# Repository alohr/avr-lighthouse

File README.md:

avr-lighthouse
==============

A photoresistor controlled LED blinker

http://ubiyubix.wordpress.com/2014/01/04/an-avr-and-photoresistor-controlled-lego-lighthouse/

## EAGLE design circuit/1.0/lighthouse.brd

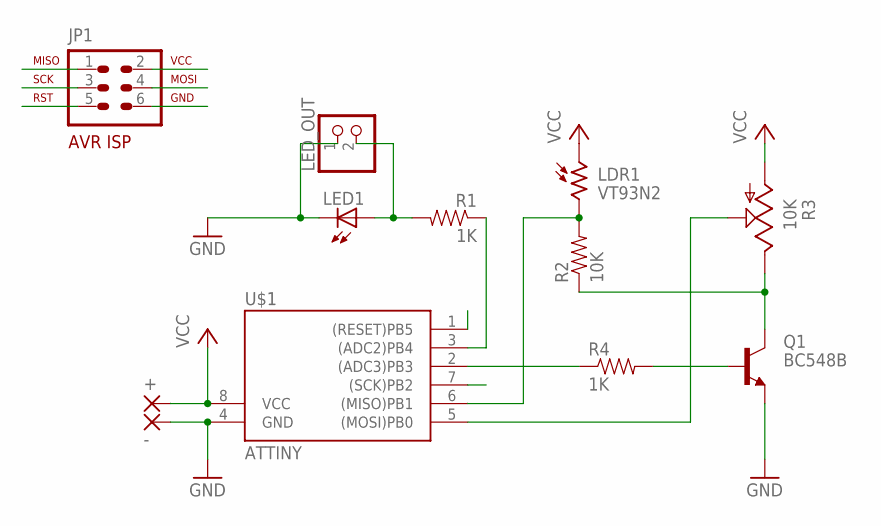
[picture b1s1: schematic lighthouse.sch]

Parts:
+: PAD-TERMINAL; 2,54/1,1
-: PAD-TERMINAL; 2,54/1,1
JP1: AVR-ISP-6VERT; AVR-ISP-6
LDR1: VT93N2; VT900
LED1: LED-3MM-NO_SILK; LED3MM-NS
LED_OUT: PINHD-1X2; 1X02; MPN BC237B
Q1: BC548B; TO92-EBC
R1, R4: 1K; AXIAL-0.4
R2: 10K; AXIAL-0.4
R3: 10K; CA6H
U$1: ATTINY; DIL08

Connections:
GND: -.1, JP1.6, LED1.K (C), LED_OUT.1, Q1.E, U$1.4 (GND)
MISO: JP1.1, LDR1.2, R2.P$2 (2), U$1.6 ((MISO)PB1)
MOSI: JP1.4, R3.S, U$1.5 ((MOSI)PB0)
unnamed: Q1.B, R4.P$2 (2)
unnamed: Q1.C, R2.P$1 (1), R3.E
unnamed: R4.P$1 (1), U$1.2 ((ADC3)PB3)
unnamed: R1.P$1 (1), U$1.3 ((ADC2)PB4)
unnamed: LED1.A, LED_OUT.2, R1.P$2 (2)
RST: JP1.5, U$1.1 ((RESET)PB5)
SCK: JP1.3, U$1.7 ((SCK)PB2)
VCC: +.1, JP1.2, LDR1.1, R3.A, U$1.8 (VCC)

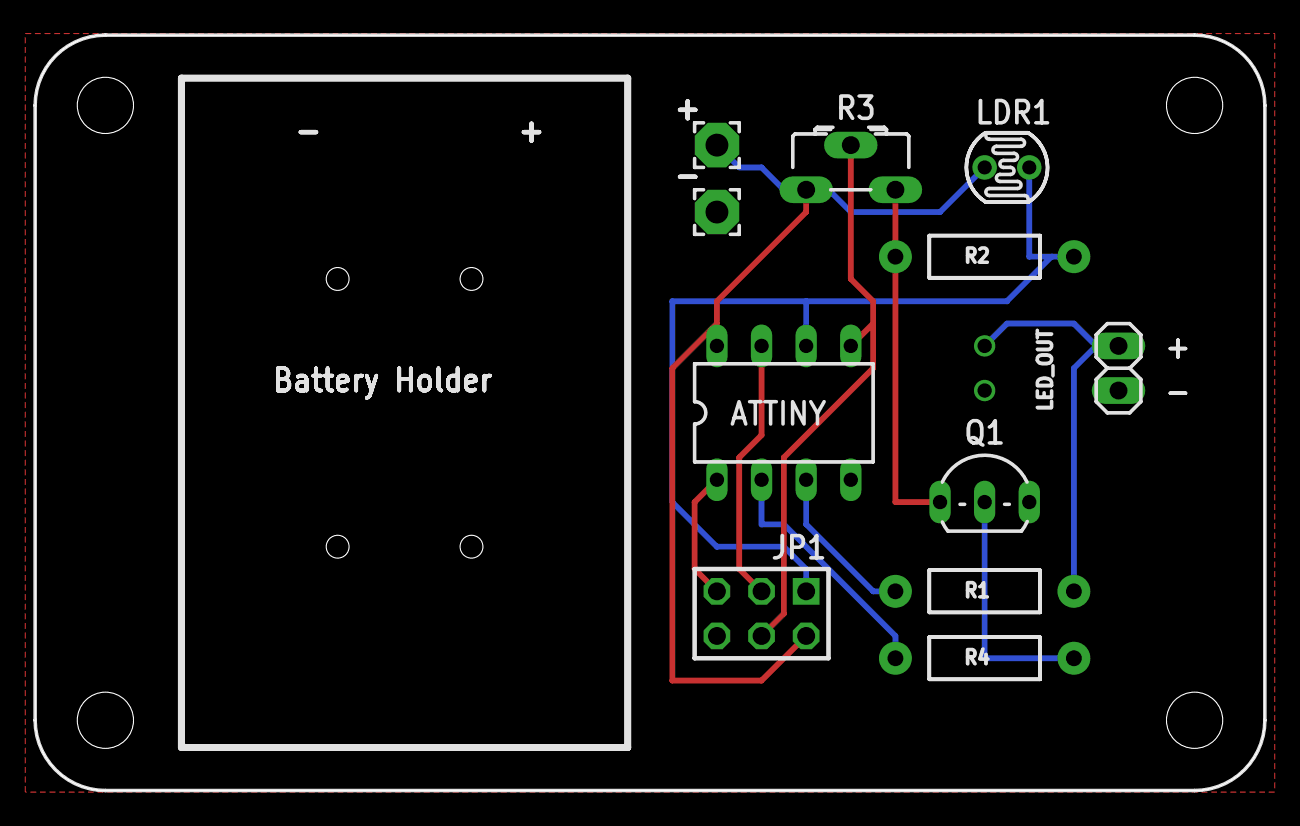
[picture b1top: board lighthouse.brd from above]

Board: 2 copper layers, 70.0 x 43.0 mm, 13 parts (0 on the bottom side), 11 nets.

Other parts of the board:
U$2: DP7043_V1

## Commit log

2014-02-15 cleanup
2014-02-15 link to schematic
2014-02-15 fixed typo
2014-02-15 link to schematic, 2nd attempt

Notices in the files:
parts and their libraries:
SparkFun-Passives: Licensing: CC v3.0 Share-Alike You are welcome to use this library for commercial purposes.
